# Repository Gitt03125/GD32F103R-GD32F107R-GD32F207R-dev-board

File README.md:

# GD32F103R GD32F107R GD32F207R development board

This board can be used with the `GD32F103Rx` and the `GD32F107Rx` , `GD32F207Rx` (Ethernet) MCU's. 

Please note that the crystal for the `GD32F107Rx` and the `GD32F207Rx` is `25MHz` and the crystal for the `GD32F103Rx` is `8MHz`.

The USB is power and DFU.

The 2x13 header is pin compatible with the Orange Pi Zero and Raspberry Pi boards. 

<table style="width:100%">
	<tr><th colspan="8">2x13 Header</th>
	</tr>
	<tr>
	<td></td>
	<td colspan="2" style="background-color:#FFA500">3.3V PWR</td>
	<td>1</td>
	<td>2</td>
	<td colspan="2" style="background-color:#FF0000">5V PWR</td>
	<td rowspan="2"></td>
	</tr>
	<tr>
	<td rowspan="2">REMAP = 0</td>
	<td style="background-color:#EE82EE">I2C0 SCA</td>
	<td>PB7</td>
	<td>3</td>
	<td>4</td>
	<td colspan="2" style="background-color:#FF0000">5V PWR</td>
	</tr>
	<tr>
	<td style="background-color:#EE82EE">I2C0 SCL</td>
	<td>PB6</td>
	<td>5</td>
	<td>6</td>
	<td colspan="2">GND</td>
	<td></td>
	</tr>
	<tr>
	<td colspan="2"></td>
	<td>PA6</td>
	<td>7</td>
	<td>8</td>
	<td>PC10</td>
	<td style="background-color:#4169E1">USART2 TX</td>
	<td rowspan="2">REMAP [1:0] =“01” (partial remap)</td>
	</tr>
	<tr>
	<td></td>
	<td colspan="2">GND</td>
	<td>9</td>
	<td>10</td>
	<td>PC11</td>
	<td style="background-color:#4169E1">USART2 RX</td>
	</tr>
	<tr>
	<td rowspan="2">REMAP = 0</td>
	<td style="background-color:#4169E1">USART5 RX</td>
	<td>PC7</td>
	<td>11</td>
	<td>12</td>
	<td>PB10</td>
	<td colspan="2"></td>
	</tr>
	<tr>
	<td style="background-color:#4169E1">USART5 TX</td>
	<td>PC6</td>
	<td>13</td>
	<td>14</td>
	<td colspan="2">GND</td>
	<td></td>
	</tr>
	<tr>
	<td colspan="2"></td>
	<td>PB14</td>
	<td>15</td>
	<td>16</td>
	<td>PB15</td>
	<td colspan="2"></td>
	</tr>
	<tr>
	<td></td>
	<td colspan="2" style="background-color:#FFA500">3.3V PWR</td>
	<td>17</td>
	<td>18</td>
	<td>PA13</td>
	<td style="background-color:#F0FFFF">SWDIO</td>
	<td></td>
	</tr>
	<tr>
	<td></td>
	<td style="background-color:#00F000">SPI2 MOSI</td>
	<td>PB5</td>
	<td>19</td>
	<td>20</td>
	<td colspan="2">GND</td>
	<td></td>
	</tr>
	<tr>
	<td></td>
	<td style="background-color:#00F000">SPI2 MISO</td>
	<td>PB4</td>
	<td>21</td>
	<td>22</td>
	<td>PA11</td>
	<td colspan="2"></td>
	</tr>
	<tr>
	<td></td>
	<td style="background-color:#00F000">SPI2 SCK</td>
	<td>PB3</td>
	<td>23</td>
	<td>24</td>
	<td>PA15</td>
	<td style="background-color:#00F000">SPI2 CS</td>
	<td></td>
	</tr>
	<tr>
	<td></td>
	<td colspan="2">GND</td>
	<td>25</td>
	<td>26</td>
	<td>PA14</td>
	<td style="background-color:#F0FFFF">SWCLK</td>
	<td></td>
	</tr>
</table>

<table>
	<tr><th colspan="4">1x13 Header</th></tr>
	<tr>
	<td>1</td>
	<td colspan="2">NC</td>
	</tr>
	<tr>
	<td>2</td>
	<td colspan="2">GND</td>
	</tr>
	<tr>
	<td>3</td>
	<td>PA14</td>
	<td style="background-color:#F0FFFF">SWCLK</td>
	</tr>
	<tr>
	<td>4</td>
	<td colspan="2">GND</td>
	</tr>
	<tr>
	<td>5</td>
	<td>PA13</td>
	<td style="background-color:#F0FFFF">SWDIO</td>
	</tr>
	<tr>
	<td>6</td>
	<td colspan="2">NRST</td>
	</tr>
	<tr>
	<td>7</td>
	<td>PA5</td>
	<td style="background-color:#FFFFEF">DAC1</td>
	</tr>
	<tr>
	<td>8</td>
	<td>PA4</td>
	<td style="background-color:#FFFFEF">DAC0</td>
	</tr>
	<tr>
	<td>9</td>
	<td>PC12</td>
	<td style="background-color:#4169E1">UART4 TX</td>
	</tr>
	<tr>
	<td>10</td>
	<td>PD2</td>
	<td style="background-color:#4169E1">UART4 RX</td>
	</tr>
	<tr>
	<td>11</td>
	<td>PB6</td>
	<td style="background-color:#4169E1">USART0 TX</td>
	<td rowspan="2">REMAP = 1</td>
	</tr>
	<tr>
	<td>12</td>
	<td>PB7</td>
	<td style="background-color:#4169E1">USART0 RX</td>
	</tr>
	<tr>
	<td>13</td>
	<td colspan="2">GND</td>
	</tr>
</table>

<table>
	<tr><th colspan="2">Boot UART</th></tr>
	<tr>
	<td>1</td>
	<td>GND</td>
	</tr>
	<tr>
	<td>2</td>
	<td style="background-color:#4169E1"> USART0 RX</td>
	<td>PA10</td>
	<td rowspan="2">REMAP = 0</td>
	</tr>
	<tr>
	<td>3</td>
	<td style="background-color:#4169E1"> USART0 TX</td>
	<td>PA9</td>
	</tr>	
</table>

<table>
<head>
	<tr>
	<th colspan="2">LED's</th>
	</tr>
</head>
<tbody>
	<tr>
	<td>1</td>
	<td>PC0</td>
	</tr>
	<tr>
	<td>2</td>
	<td>PC2</td>
	</tr>
	<tr>
	<td>3</td>
	<td>PC3</td>
	</tr>
	<tr>
	<td>4</td>
	<td>3V3</td>
	</tr>	
</tbody>
</table>

<table>
	<tr><th colspan="4">2x7 Header</th></tr>
	<tr>
	<td>PB13</td>
	<td>1</td>
	<td>2</td>
	<td>NC</td>
	</tr>
	<tr>
	<td>PB11</td>
	<td>3</td>
	<td>4</td>
	<td>PB12</td>
	</tr>
	<tr>
	<td>PC4</td>
	<td>5</td>
	<td>6</td>
	<td>PC5</td>
	</tr>
	<tr>
	<td>PA1</td>
	<td>7</td>
	<td>8</td>
	<td>PA7</td>
	</tr>
	<tr>
	<td>PA2</td>
	<td>9</td>
	<td>10</td>
	<td>PC1</td>
	</tr>
	<tr>
	<td>GND</td>
	<td>11</td>
	<td>12</td>
	<td>GND</td>
	</tr>
	<tr>
	<td style="background-color:#FFA500">3V3</td>
	<td>13</td>
	<td>14</td>
	<td style="background-color:#FFA500">3V3</td>
	</tr>	
</table>

### GD32F103Rx (only)

<table>
<head>
<tr><th colspan="5">1x4 Header</th></tr>
</head>
<tbody>
<tr>
<td></td>
<td>GND</td>
<td>1</td>
<td>GND</td>
<td></td>
</tr>
<tr>
<td></td>
<td style="background-color:#FFA500">3V3</td>
<td>2</td>
<td style="background-color:#FFA500">3V3</td>
<td></td>
</tr>
<tr>
<td rowspan="2">REMAP[1:0] = 00/01</td>
<td style="background-color:#EE82EE">I2C1 SCL</td>
<td>3</td>
<td style="background-color:#4169E1">USART2 RX</td>
<td rowspan="2">REMAP = 0 (no remap)</td>
</tr>
<tr>
<td style="background-color:#EE82EE">I2C1 SCA</td>
<td>4</td>
<td style="background-color:#4169E1">USART2 TX</td>
</tr>	
</tbody>
</table>

### GD32F107Rx GD32F207Rx (only)

<table>
<head>
<tr>
<th colspan="4">External-PHY</th>
</tr>
</head>
<tbody>
<tr>
<td>RMII TXD1</td>
<td>1</td>
<td>2</td>
<td>NC</td>
</tr>
<tr>
<td>RMII TX_EN</td>
<td>3</td>
<td>4</td>
<td>RMII TXD0</td>
</tr>
<tr>
<td>RMII RXD0</td>
<td>5</td>
<td>6</td>
<td>RMII RXD1</td>
</tr>
<tr>
<td>RMII REF_CLK</td>
<td>7</td>
<td>8</td>
<td>RMII CRS_DV</td>
</tr>
<tr>
<td>MDIO</td>
<td>9</td>
<td>10</td>
<td>MDC</td>
</tr>
<tr>
<td>GND</td>
<td>11</td>
<td>12</td>
<td>GND</td>
</tr>
<tr>
<td style="background-color:#FFA500">3V3</td>
<td>13</td>
<td>14</td>
<td style="background-color:#FFA500">3V3</td>
</tr>		
</tbody>
</table>

[PayPal.Me Donate](https://paypal.me/AvanVught?locale.x=nl_NL)

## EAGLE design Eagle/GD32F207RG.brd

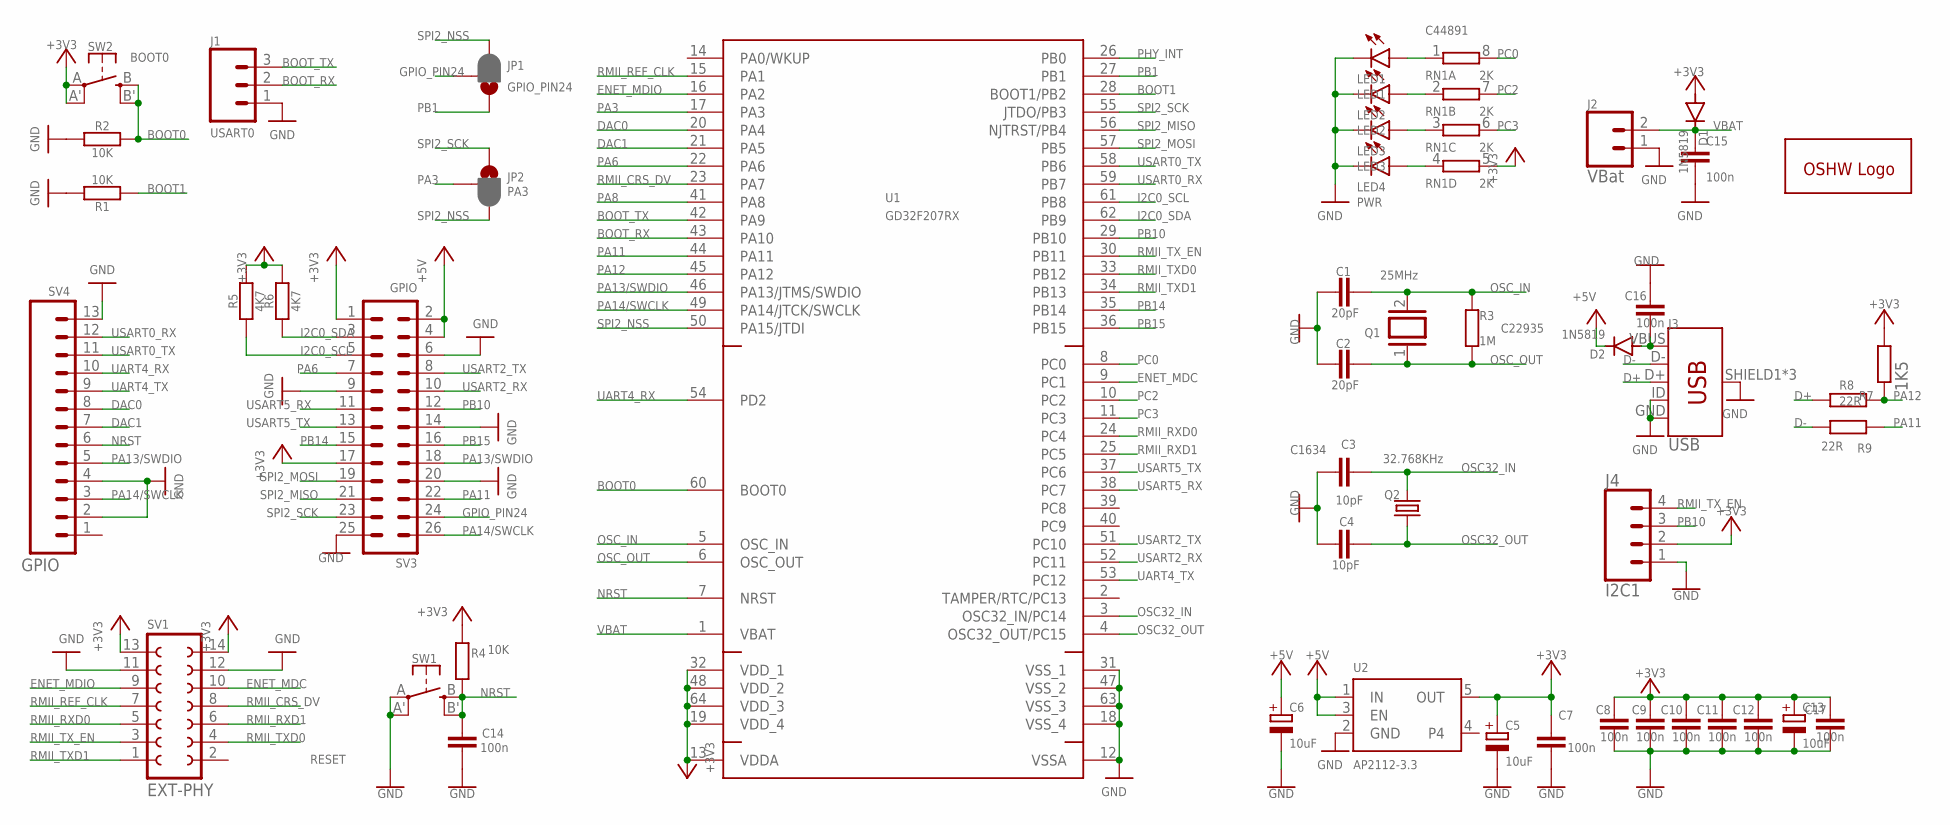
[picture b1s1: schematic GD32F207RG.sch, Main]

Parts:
C1, C2: 20pF; C0603; JLCPCB C1648
C3, C4: 10pF; C0603; JLCPCB C1634
C5, C6, C13: 10uF; A/3216-18R; JLCPCB C7171
C7, C8, C9, C10, C11, C12, C14, C15, C16, C17: 100n; C0603; JLCPCB C14663
D1, D2: 1N5819; SOD323-R; JLCPCB C191023
GOLD_ORB_SM1: OSHWLOGOLOGO5MM; OSHW_5MM
J1: USART0; 1X03
J2: VBat; JST-2-PTH
J3: USB; USB-B-MICRO-SMD; JLCPCB C404968
J4: I2C1; 1X04
JP1: GPIO_PIN24; SMT-JUMPER_3_1-NC_PASTE_SILK
JP2: PA3; SMT-JUMPER_3_1-NC_PASTE_SILK
LED1: LED1; CHIP-LED0603
LED2: LED2; CHIP-LED0603
LED3: LED3; CHIP-LED0603
LED4: PWR; CHIP-LED0603
Q1: 25MHz; QS
Q2: 32.768KHz; TC26H
R1, R2, R4: 10K; R0603; JLCPCB C25804
R3: 1M; R0603; JLCPCB C22935
R5, R6: 4K7; R0603; JLCPCB C23162
R7: 1K5; R0603; JLCPCB C4190
R8, R9: 22R; R0603; JLCPCB C23345
RN1: 2K; 4X0402ARV341; JLCPCB C44891
SV1: EXT-PHY; FE07-2W
SV3: GPIO; MA13-2
SV4: GPIO; 1X13
SW1: RESET; EVQ-Q2
SW2: BOOT0; EVQ-Q2; JLCPCB C221880
U1: GD32F207RX; LQFP64
U2: AP2112-3.3; SOT23-5; JLCPCB C51118

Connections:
+3V3: C5.+, C7.1, C8.1, C9.1, C10.1, C11.1, C12.1, C13.+, C17.1, D1.A, J4.2, R4.2, R5.2, R6.2, R7.2, RN1.5 (2), SV1.13, SV1.14, SV3.1, SV3.17, SW2.A, SW2.A' (P1), U1.13 (VDDA), U1.19 (VDD_4), U1.32 (VDD_1), U1.48 (VDD_2), U1.64 (VDD_3), U2.5 (OUT)
+5V: C6.+, D2.C, SV3.2, SV3.4, U2.1 (IN), U2.3 (EN)
BOOT0: R2.2, SW2.B (S), SW2.B' (S1), U1.60 (BOOT0)
BOOT1: R1.1, U1.28 (BOOT1/PB2)
BOOT_RX: J1.2, U1.43 (PA10)
BOOT_TX: J1.3, U1.42 (PA9)
D+: J3.D+, R8.1
D-: J3.D-, R9.1
DAC0: SV4.8, U1.20 (PA4)
DAC1: SV4.7, U1.21 (PA5)
ENET_MDC: SV1.10, U1.9 (PC1)
ENET_MDIO: SV1.9, U1.16 (PA2)
GND: C1.1, C2.1, C3.1, C4.1, C5.-, C6.-, C7.2, C8.2, C9.2, C10.2, C11.2, C12.2, C13.-, C14.2, C15.2, C16.1, C17.2, J1.1, J2.1, J3.GND, J3.ID, J3.SHIELD1 (SHIELD), J3.SHIELD2 (SHIELD), J3.SHIELD3 (SHIELD), J4.1, LED1.C, LED2.C, LED3.C, LED4.C, R1.2, R2.1, SV1.11, SV1.12, SV3.6, SV3.9, SV3.14, SV3.20, SV3.25, SV4.2, SV4.4, SV4.13, SW1.A, SW1.A' (P1), U1.12 (VSSA), U1.18 (VSS_4), U1.31 (VSS_1), U1.47 (VSS_2), U1.63 (VSS_3), U2.2 (GND)
GPIO_PIN24: JP1.2, SV3.24
I2C0_SCL: R5.1, SV3.5, U1.61 (PB8)
I2C0_SDA: R6.1, SV3.3, U1.62 (PB9)
unnamed: LED1.A, RN1.1
unnamed: LED2.A, RN1.2 (1)
unnamed: LED3.A, RN1.3 (1)
unnamed: LED4.A, RN1.4 (1)
NRST: C14.1, R4.1, SV4.6, SW1.B (S), SW1.B' (S1), U1.7 (NRST)
OSC32_IN: C3.2, Q2.2, U1.3 (OSC32_IN/PC14)
OSC32_OUT: C4.2, Q2.1, U1.4 (OSC32_OUT/PC15)
OSC_IN: C1.2, Q1.2, R3.2, U1.5 (OSC_IN)
OSC_OUT: C2.2, Q1.1, R3.1, U1.6 (OSC_OUT)
PA3: JP2.2, U1.17 (PA3)
PA6: SV3.7, U1.22 (PA6)
PA8: U1.41 (PA8)
PA11: R9.2, SV3.22, U1.44 (PA11)
PA12: R7.1, R8.2, U1.45 (PA12)
PA13/SWDIO: SV3.18, SV4.5, U1.46 (PA13/JTMS/SWDIO)
PA14/SWCLK: SV3.26, SV4.3, U1.49 (PA14/JTCK/SWCLK)
PB1: JP1.1, U1.27 (PB1)
PB10: J4.3, SV3.12, U1.29 (PB10)
PB14: SV3.15, U1.35 (PB14)
PB15: SV3.16, U1.36 (PB15)
PC0: RN1.8 (2), U1.8 (PC0)
PC2: RN1.7 (2), U1.10 (PC2)
PC3: RN1.6 (2), U1.11 (PC3)
PHY_INT: U1.26 (PB0)
RMII_CRS_DV: SV1.8, U1.23 (PA7)
RMII_REF_CLK: SV1.7, U1.15 (PA1)
RMII_RXD0: SV1.5, U1.24 (PC4)
RMII_RXD1: SV1.6, U1.25 (PC5)
RMII_TXD0: SV1.4, U1.33 (PB12)
RMII_TXD1: SV1.1, U1.34 (PB13)
RMII_TX_EN: J4.4, SV1.3, U1.30 (PB11)
SPI2_MISO: SV3.21, U1.56 (NJTRST/PB4)
SPI2_MOSI: SV3.19, U1.57 (PB5)
SPI2_NSS: JP1.3, JP2.3, U1.50 (PA15/JTDI)
SPI2_SCK: JP2.1, SV3.23, U1.55 (JTDO/PB3)
UART4_RX: SV4.10, U1.54 (PD2)
UART4_TX: SV4.9, U1.53 (PC12)
USART0_RX: SV4.12, U1.59 (PB7)
USART0_TX: SV4.11, U1.58 (PB6)
USART2_RX: SV3.10, U1.52 (PC11)
USART2_TX: SV3.8, U1.51 (PC10)
USART5_RX: SV3.11, U1.38 (PC7)
USART5_TX: SV3.13, U1.37 (PC6)
VBAT: C15.1, D1.C, J2.2, U1.1 (VBAT)
VBUS: C16.2, D2.A, J3.VBUS

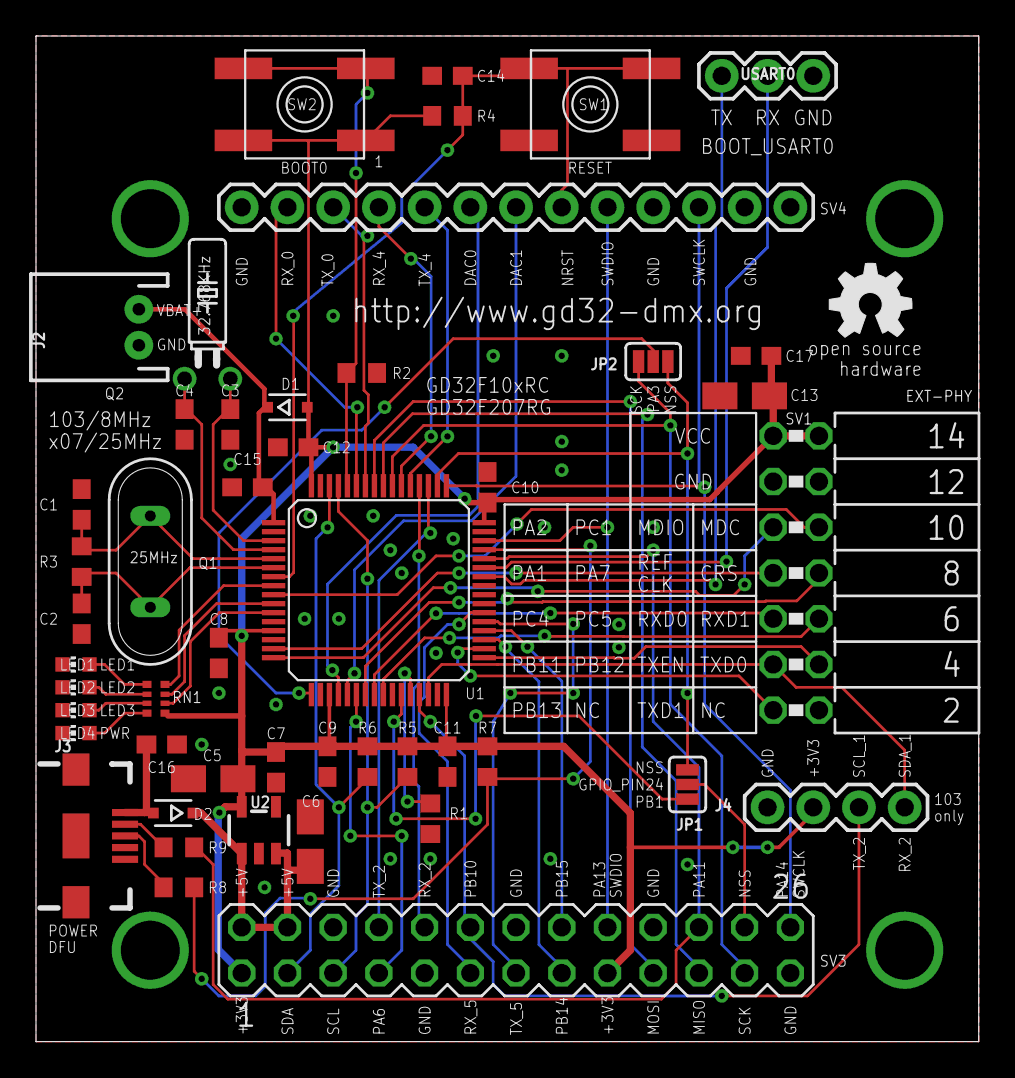
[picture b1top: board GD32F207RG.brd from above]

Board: 2 copper layers, 52.4 x 55.9 mm, 49 parts (0 on the bottom side), 59 nets.

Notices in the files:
parts and their libraries:
SparkFun-Connectors: Licensing: Creative Commons ShareAlike 4.0 International - https://creativecommons.org/licenses/by-sa/4.0
microbuilder: This work is placed in the public domain, and may be freely used for commercial and non-commercial work with the following conditions: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
